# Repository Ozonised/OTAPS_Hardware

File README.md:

# OTAPS - Open Train Accident Prevention System
This repository contains schematic, PCB and wiring files for OTAPS.

## Directory info:
1. ```Wiring``` contains the schematic for wiring signal node.
2. ```WiringLocomotiveUnit``` contains the schematic for wiring the locomotive unit.
3. ```Nodes``` contains the schematic and PCBs files for the PCBs.

# DETAILS:
I created this project for the **Circuit Digest 2024 IoT & Edge AI Project Challenge**.
The firmware for the signal and locomotive units is available at this repository: https://github.com/Ozonised/OTAPS_Firmware
The project details including features, working protocol, build guide and code explanation can be found on this page: https://circuitdigest.com/microcontroller-projects/otaps-open-train-accident-prevention-system

### NOTE:
Both signal and locomotive units utilise the same PCB.

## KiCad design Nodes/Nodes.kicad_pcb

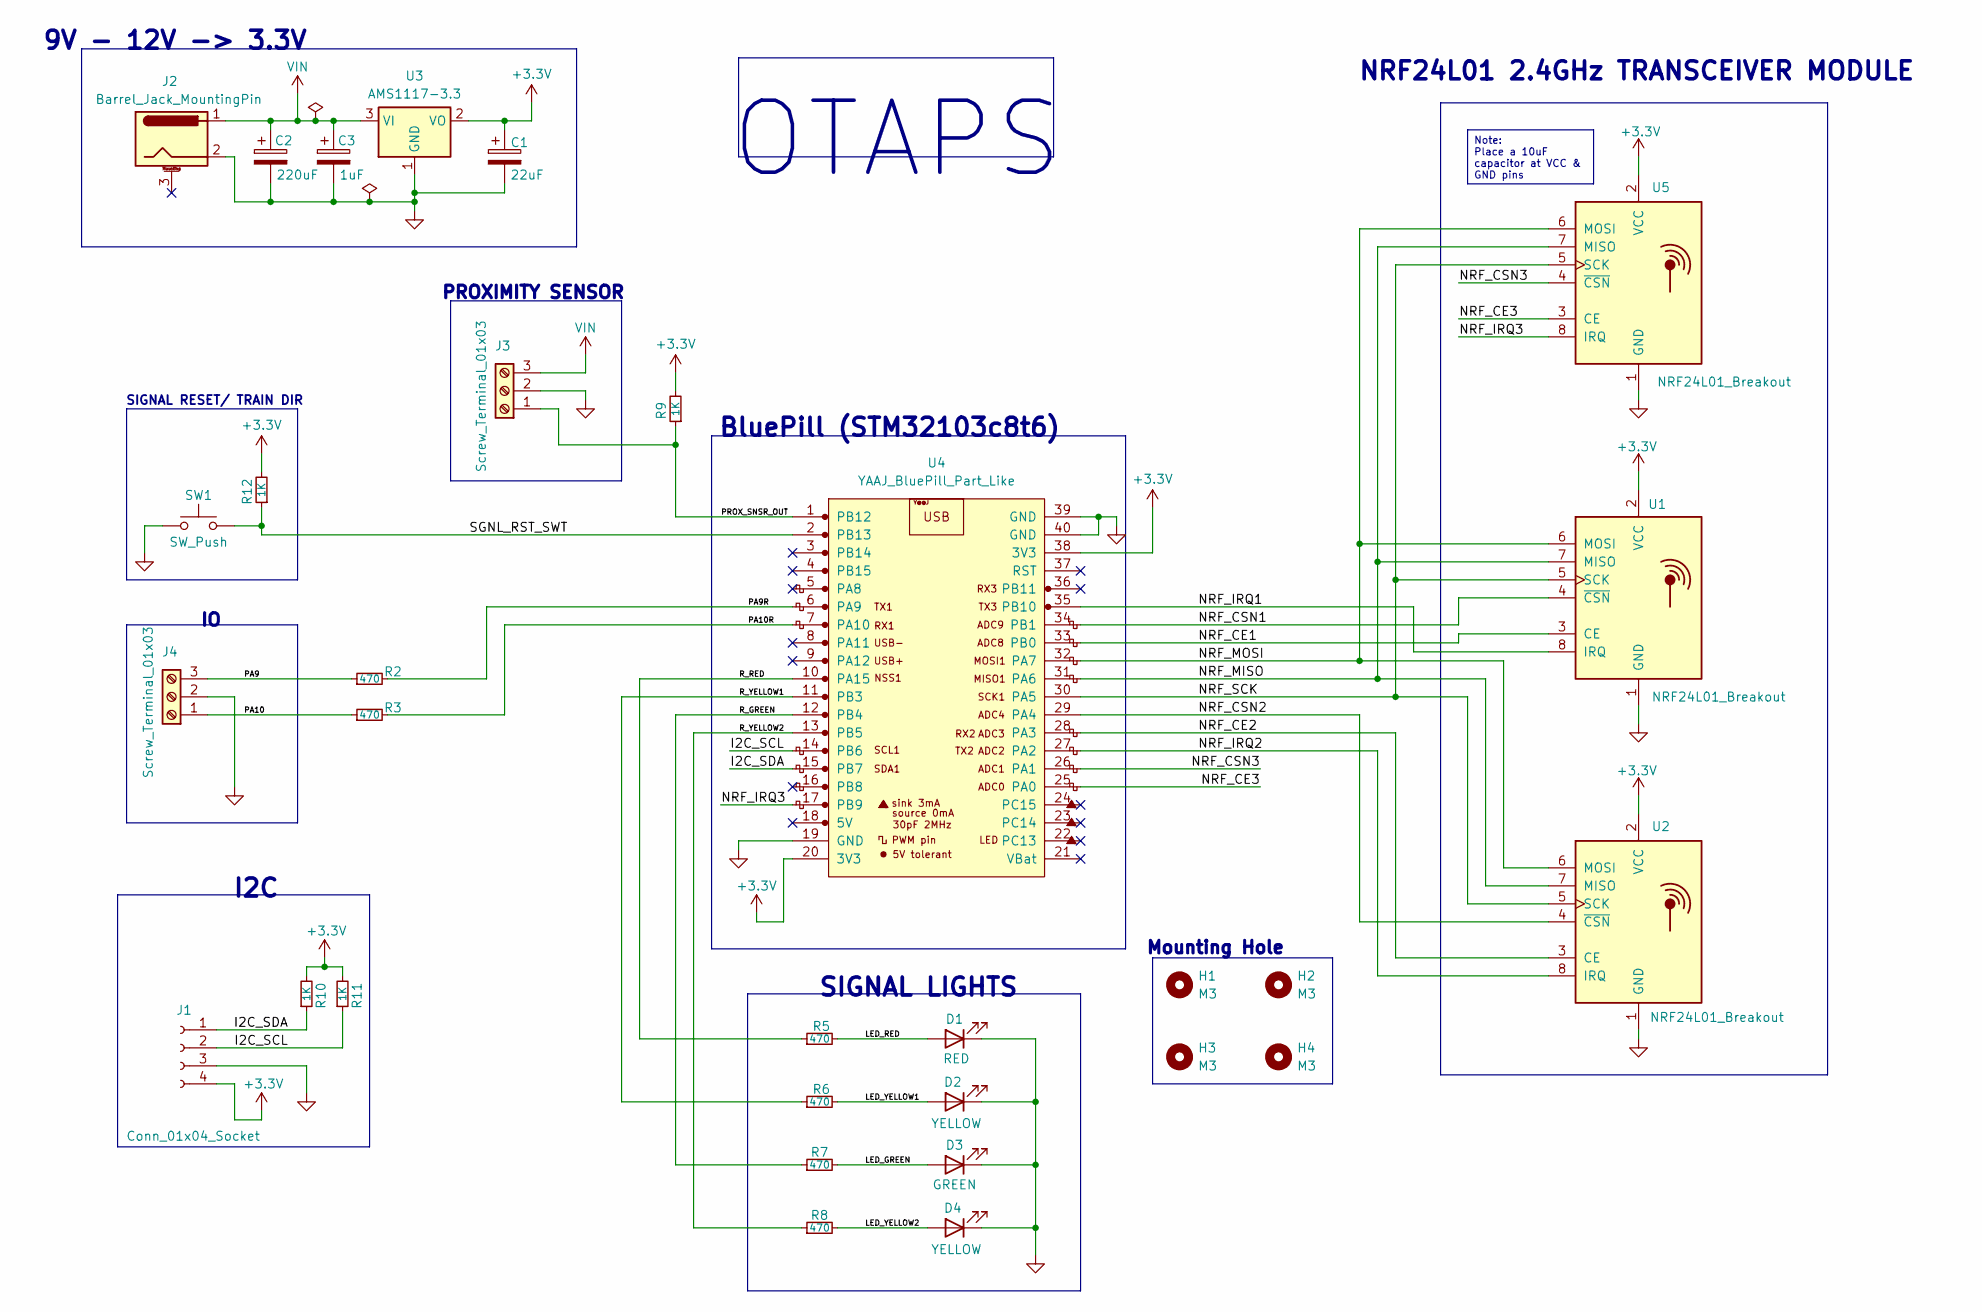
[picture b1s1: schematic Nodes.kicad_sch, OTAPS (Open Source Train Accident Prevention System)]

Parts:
C1: 22uF; CP_EIA-3528-15_AVX-H_Pad1.50x2.35mm_HandSolder
C2: 220uF; CP_Elec_8x10.5
C3: 1uF; C_1206_3216Metric_Pad1.33x1.80mm_HandSolder
D1: RED; LED_D3.0mm
D2, D4: YELLOW; LED_D3.0mm
D3: GREEN; LED_D3.0mm
H1, H2, H3, H4: M3; MountingHole_3.2mm_M3
J1: Conn_01x04_Socket; PinSocket_1x04_P2.54mm_Vertical
J2: Barrel_Jack_MountingPin; BarrelJack_Horizontal
J3, J4: Screw_Terminal_01x03
R2, R3, R5, R6, R7, R8: 470; R_0805_2012Metric_Pad1.20x1.40mm_HandSolder
R9, R10, R11, R12: 1K; R_0805_2012Metric_Pad1.20x1.40mm_HandSolder
SW1: SW_Push; SW_SPST_PTS647_Sx38
U1, U2, U5: NRF24L01_Breakout; nRF24L01_Breakout
U3: AMS1117-3.3; SOT-223-3_TabPin2
U4: YAAJ_BluePill_Part_Like; YAAJ_BluePill_1

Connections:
+3.3V: C1.1, J1.4, R9.2, R10.2, R11.2, R12.2, U1.2 (VCC), U2.2 (VCC), U3.2 (VO), U4.20 (3V3), U4.38 (3V3), U5.2 (VCC)
/I2C_SCL: J1.2, R11.1, U4.14 (PB6)
/I2C_SDA: J1.1, R10.1, U4.15 (PB7)
/LED_GREEN: D3.2 (A), R7.2
/LED_RED: D1.2 (A), R5.2
/LED_YELLOW1: D2.2 (A), R6.2
/LED_YELLOW2: D4.2 (A), R8.2
/NRF_CE1: U1.3 (CE), U4.33 (PB0)
/NRF_CE2: U2.3 (CE), U4.28 (PA3)
/NRF_CE3: U4.25 (PA0), U5.3 (CE)
/NRF_CSN1: U1.4 (~CSN), U4.34 (PB1)
/NRF_CSN2: U2.4 (~CSN), U4.29 (PA4)
/NRF_CSN3: U4.26 (PA1), U5.4 (~CSN)
/NRF_IRQ1: U1.8 (IRQ), U4.35 (PB10)
/NRF_IRQ2: U2.8 (IRQ), U4.27 (PA2)
/NRF_IRQ3: U4.17 (PB9), U5.8 (IRQ)
/NRF_MISO: U1.7 (MISO), U2.7 (MISO), U4.31 (PA6), U5.7 (MISO)
/NRF_MOSI: U1.6 (MOSI), U2.6 (MOSI), U4.32 (PA7), U5.6 (MOSI)
/NRF_SCK: U1.5 (SCK), U2.5 (SCK), U4.30 (PA5), U5.5 (SCK)
/PA9: J4.3, R2.1
/PA9R: R2.2, U4.6 (PA9)
/PA10: J4.1, R3.1
/PA10R: R3.2, U4.7 (PA10)
/PROX_SNSR_OUT: J3.1, R9.1, U4.1 (PB12)
/R_GREEN: R7.1, U4.12 (PB4)
/R_RED: R5.1, U4.10 (PA15)
/R_YELLOW1: R6.1, U4.11 (PB3)
/R_YELLOW2: R8.1, U4.13 (PB5)
/SGNL_RST_SWT: R12.1, SW1.2, U4.2 (PB13)
GND: C1.2, C2.2, C3.2, D1.1 (K), D2.1 (K), D3.1 (K), D4.1 (K), J1.3, J2.2, J3.2, J4.2, SW1.1, U1.1 (GND), U2.1 (GND), U3.1 (GND), U4.19 (GND), U4.39 (GND), U4.40 (GND), U5.1 (GND)
VIN: C2.1, C3.1, J2.1, J3.3, U3.3 (VI)

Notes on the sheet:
Note: Place a 10uF capacitor at VCC & GND pins
NRF24L01 2.4GHz TRANSCEIVER MODULE
SIGNAL LIGHTS
9V - 12V -> 3.3V
I2C
BluePill (STM32103c8t6)
OTAPS
Mounting Hole
PROXIMITY SENSOR
SIGNAL RESET/ TRAIN DIR

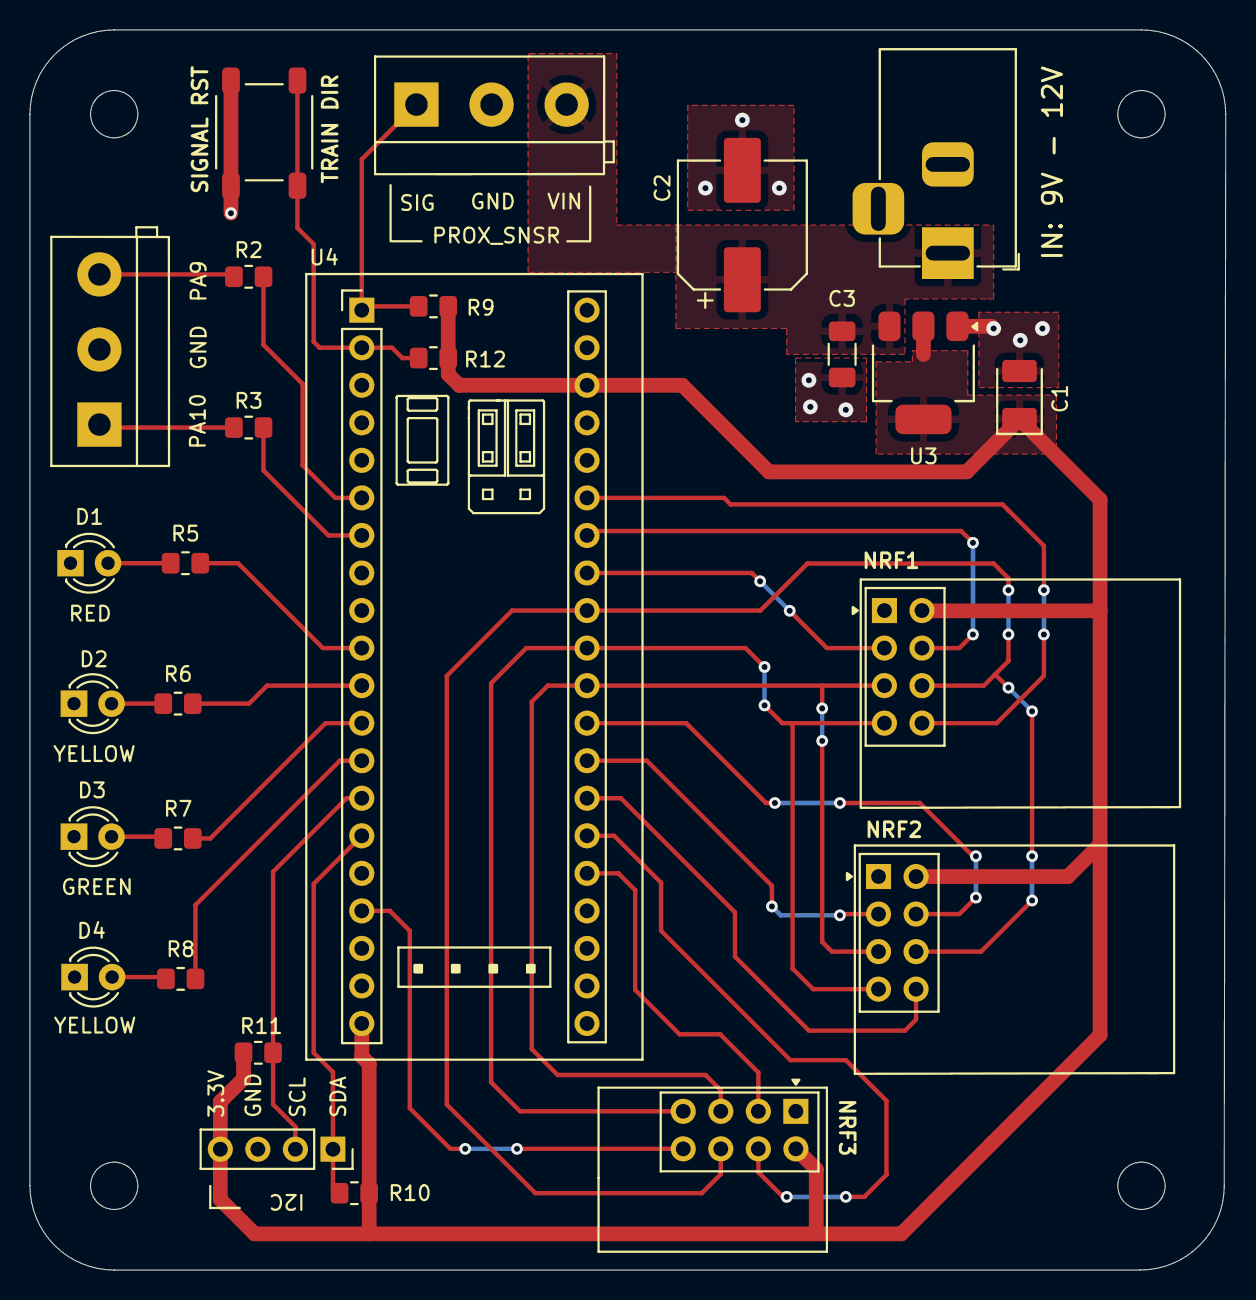
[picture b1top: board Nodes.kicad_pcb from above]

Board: 2 copper layers, 80.9 x 83.9 mm, 31 parts (0 on the bottom side), 31 nets.

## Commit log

2024-09-20 chore: initial commit
2024-09-20 docs: add license
2024-09-20 docs: add readme
2024-09-20 chore: update GitHub repository path
2024-09-20 chore: add author, licensce and GitHub repository info
2024-09-20 fix: remove 3.3V connection between arduino & signal node
    The signal node and the arduino should be powered from the barrel connector.
    Also added a note regarding this to the schematic.
2024-09-20 fix: update the node schematic symbol as per rev 1.1
2024-09-21 chore: add labels to switch
    rename OLED port on pcb to I2C, added "TRAIN DIR" text to switch on schematic and PCB.
2024-09-21 docs: add directory information
2024-09-25 chore: change connections for NRF24(U5), IO port and LEDs
2024-09-27 fix: change silkscreen line width to 0.152 and update vendor link for resistors and NRF24
2024-10-02 docs: add details section
    add links to firmware repo and the circuit digest project page
2024-10-18 fix: change switch footprint changed the switch footprint and associated 3D model regenerated the gerbers
2024-11-02 docs: add project image
2024-11-12 docs: add link to project documentation

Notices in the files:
Nodes/Nodes.kicad_pcb:
License: GNU General Public License version 3
